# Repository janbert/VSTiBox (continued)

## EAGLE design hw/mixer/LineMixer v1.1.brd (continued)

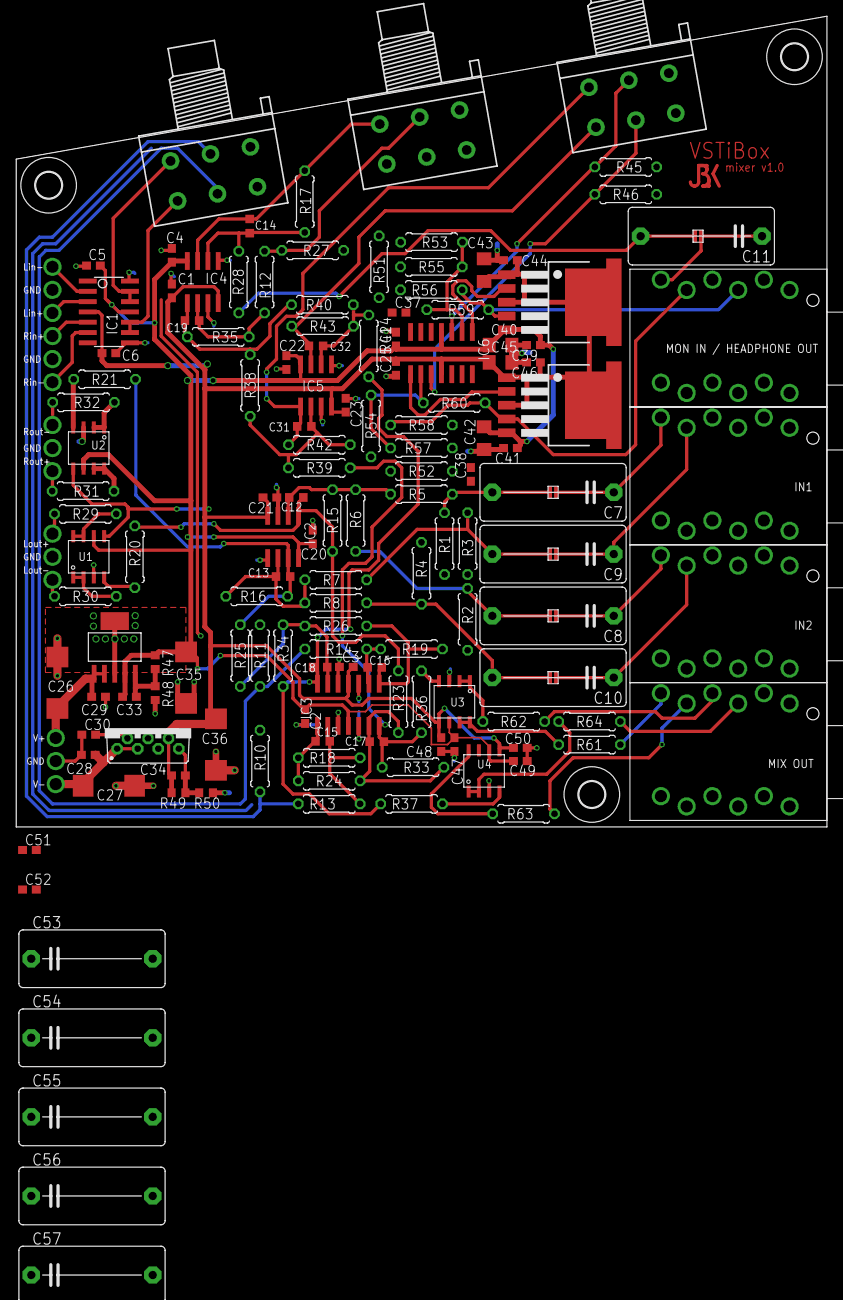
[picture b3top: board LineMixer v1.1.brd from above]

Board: 2 copper layers, 100.0 x 100.0 mm, 163 parts (0 on the bottom side), 86 nets.

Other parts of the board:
U$9: JBK_LOGO_SMALL_COPPER

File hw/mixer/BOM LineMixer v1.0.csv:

Qty;Value;Device;Package;Parts;Description
4;;NSJ12HF-1;NSJ12HF-1;U$1, U$2, U$3, U$6;Stereo dual jack, full threaded nose
1;1.62M;R-EU_R0603;R0603;R49;RESISTOR, European symbol
8;100R;R-EU_0207/7;0207/7;R29, R30, R31, R32, R61, R62, R63, R64;RESISTOR, European symbol
8;100k;R-EU_0207/7;0207/7;R1, R2, R3, R4, R10, R27, R45, R46;RESISTOR, European symbol
1;100k\;R-EU_0207/7;0207/7;R11;RESISTOR, European symbol
20;100n;C-EUC0603;C0603;C1, C2, C3, C4, C5, C6, C20, C21, C22, C23, C24, C25, C39, C41, C44, C46, C47, C48, C49, C50;CAPACITOR, European symbol
2;100nF;C-EUC0603;C0603;C28, C29;CAPACITOR, European symbol
6;10k;R-EU_0207/7;0207/7;R13, R14, R18, R19, R28, R35;RESISTOR, European symbol
3;10k log;3RP/1610G;3RP/1610G;R9, R22, R44;16mm Potentiometer two level
2;10nF;C-EUC0603;C0603;C33, C34;CAPACITOR, European symbol
4;1M;R-EU_0207/7;0207/7;R51, R52, R56, R58;RESISTOR, European symbol
6;1k;R-EU_0207/7;0207/7;R53, R54, R55, R57, R59, R60;RESISTOR, European symbol
2;1uF;C-EUC0603;C0603;C30, C38;CAPACITOR, European symbol
1;1uf;C-EUC0603;C0603;C37;CAPACITOR, European symbol
1;20k8;R-EU_R0603;R0603;R47;RESISTOR, European symbol
1;215k;R-EU_R0603;R0603;R50;RESISTOR, European symbol
7;220p;C-EUC0603K;C0603K;C12, C13, C14, C17, C18, C31, C32;CAPACITOR, European symbol
2;220uF;CPOL-EUD/7343-31R;D/7343-31R;C35, C36;POLARIZED CAPACITOR, European symbol
22;2k49;R-EU_0207/7;0207/7;R5, R6, R7, R8, R12, R17, R20, R21, R23, R24, R25, R26, R33, R34, R36, R37, R38, R39, R40, R41, R42, R43;RESISTOR, European symbol
1;2k87;R-EU_R0603;R0603;R48;RESISTOR, European symbol
5;4.7uF;C15/7;C15B7;C7, C8, C9, C10, C11;CAPACITOR
3;47p;C-EUC0603K;C0603K;C15, C16, C19;CAPACITOR, European symbol
2;47uF;CPOL-EUD/7343-31R;D/7343-31R;C26, C27;POLARIZED CAPACITOR, European symbol
2;4k99;R-EU_0207/7;0207/7;R15, R16;RESISTOR, European symbol
4;4u7 16V;C-EUC1206;C1206;C40, C42, C43, C45;CAPACITOR, European symbol
4;DRV134SO-8;DRV134SO-8;SO-8;U1, U2, U3, U4;
1;INA2134-EP;INA2134U;SO14;IC1;Audio Differential Line Receivers
2;LM4558D;LM4558D;SO08;IC2, IC5;OP AMP
1;LM4562;LM4558D;SO08;IC4;OP AMP
2;LME49600;LME49600;TS5B;IC7, IC8;High Performance, High Fidelity, High Current Audio Buffer
2;LME49740;TL074D;SO14;IC3, IC6;OP AMP
3;MOUNT-HOLE3.2;MOUNT-HOLE3.2;3,2;H1, H3, H4;MOUNTING HOLE with drill center marker
15;PAD1.5MM;PAD1.5MM;PAD_1.5MM;U$7, U$8, U$10, U$11, U$12, U$13, U$14, U$15, U$16, U$17, U$18, U$19, U$20, U$21, U$22;
5;SOLDERLINK;SOLDERLINK;SOLDERLINK;S1, S2, S3, S4, S5;
1;TPS7A3301KC;TPS7A3301KC;TO220-7;U$4;Ultralow-Noise Negative Voltage Regulator v3
1;TPS7A4501;TPS7A4501;SOT223-5;U$5;LOW-NOISE FAST-TRANSIENT-RESPONSE 1.5-A LOW-DROPOUT VOLTAGE

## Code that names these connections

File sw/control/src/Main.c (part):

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#define BTN2	(!(GPIOGetValue(2, 5)))		//	P2.5
#define BTN3	(!(GPIOGetValue(3, 1)))		//	P3.1
#define BTN4	(!(GPIOGetValue(2, 7)))		//	P2.7
#define E1_I	(!(GPIOGetValue(2, 10)))	//	P2.10
#define E2_I	(!(GPIOGetValue(2, 2)))		//	P2.2
#define E3_I	(!(GPIOGetValue(3, 2)))		//	P3.2
#define E4_I	(!(GPIOGetValue(3, 4)))		//  P3.4

#define CMD_SET_ID 		(0 | (1<<7))		// 0x80
#define CMD_BTN 			(1 | (1<<7))		// 0x81
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	GPIOSetDir(2, 7, 0);		// BTN4
	LPC_IOCON->PIO2_7 = PULL_UP | FUNC0;
	
	GPIOSetDir(2, 10, 0);		// E1_I
	LPC_IOCON->PIO2_10 = PULL_UP | FUNC0;
	
	GPIOSetDir(2, 2, 0);		// E2_I
	LPC_IOCON->PIO2_2 = PULL_UP | FUNC0;

	GPIOSetDir(3, 2, 0);		// E3_I
	LPC_IOCON->PIO3_2 = PULL_UP | FUNC0;

	GPIOSetDir(3, 4, 0);		// E4_I	
	LPC_IOCON->PIO3_4 = PULL_UP | FUNC0;
	
	GPIOSetDir(0, 7, 0);		// E1_A
	LPC_IOCON->PIO0_7 = PULL_UP | FUNC0;
	
	GPIOSetDir(0, 6, 0);		// E2_A
	LPC_IOCON->PIO0_6 = PULL_UP | FUNC0;
	
	GPIOSetDir(3, 0, 0);		// E3_A
	LPC_IOCON->PIO3_0 = PULL_UP | FUNC0;
	
	GPIOSetDir(2, 11, 0);		// E4_A
	LPC_IOCON->PIO2_11 = PULL_UP | FUNC0;
	
	GPIOSetDir(2, 9, 0);		// E1_B
	LPC_IOCON->PIO2_9 = PULL_UP | FUNC0;
	
	GPIOSetDir(2, 1, 0);		// E2_B
	LPC_IOCON->PIO2_1 = PULL_UP | FUNC0;
	
	GPIOSetDir(2, 3, 0);		// E3_B
	LPC_IOCON->PIO2_3 = PULL_UP | FUNC0;
	
	GPIOSetDir(3, 3, 0);		// E4_B
	LPC_IOCON->PIO3_3 = PULL_UP | FUNC0;
}

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
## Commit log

2018-09-04 Added hw sources
2018-09-04 Added host .NET
2018-09-04 Added contol c source
2018-09-05 Added files for lasercutting
2018-09-26 Added missing DLL's and updated main window controls
2018-09-26 Added folder to gitignore
2018-09-26 Added missing file
2018-10-04 Restored record function
2018-10-04 Fixed VST program name display
2018-10-04 Updated gitignore
2018-10-05 Fixed BPM bug, fixed large VST window size
2018-10-23 Fixed empty program name bug. Fixed unloading editor for recyled VST
2018-11-04 Added expression invert in keyzone control. Renamed ControPedalAction to ExpressionPedalFunction
2018-11-06 Plugin MainsChanged and StartProcess now after audio buffer creation, fixing stability issues.
2018-11-06 Updated to version 2.1
2018-12-18 WIP on keyboard velocity
2018-12-23 Experimental onsong support. Finished midi velocity setting.
2018-12-23 Added experimental onsong support missing updates
2019-09-25 Added try catch for failing instrument load
2019-10-07 Added missing plugins cleanup
2019-11-09 Targeted VS2017
2019-11-09 Added large address aware post build step
2019-11-09 Update Gitignore
2020-12-04 VSTiBoard initial commit
